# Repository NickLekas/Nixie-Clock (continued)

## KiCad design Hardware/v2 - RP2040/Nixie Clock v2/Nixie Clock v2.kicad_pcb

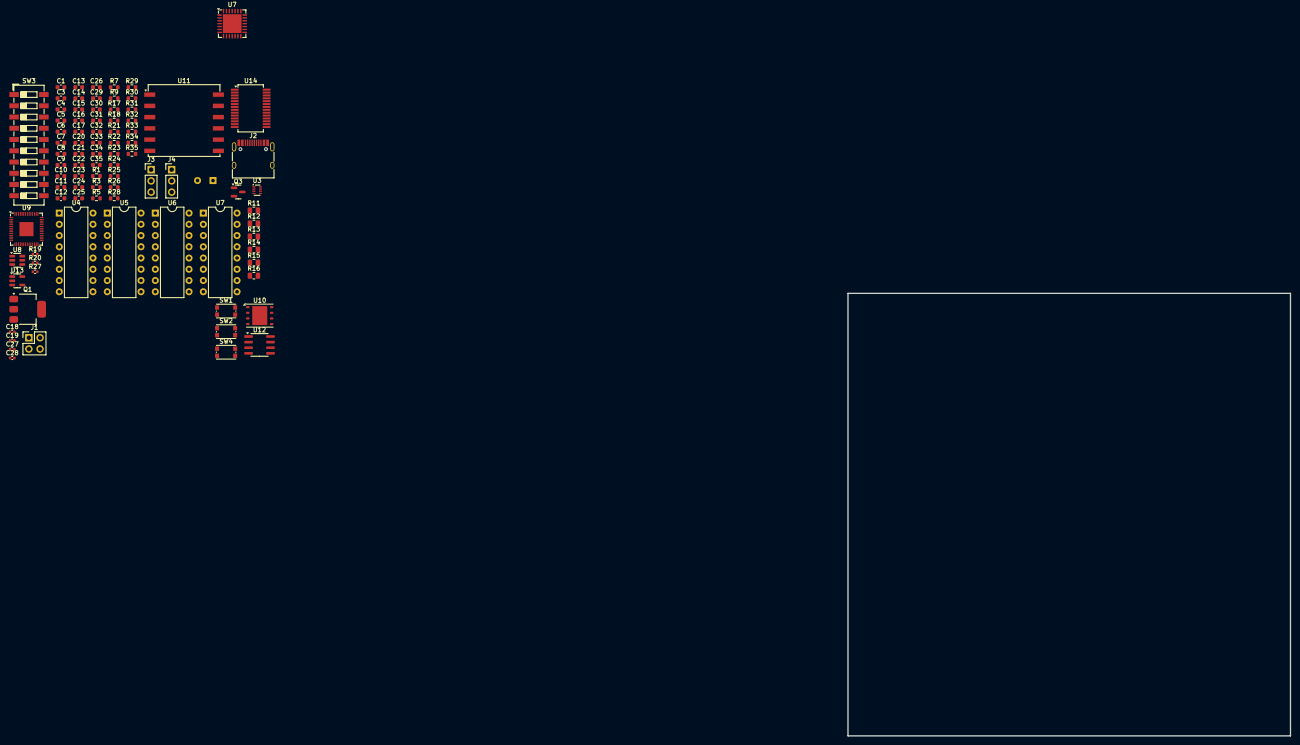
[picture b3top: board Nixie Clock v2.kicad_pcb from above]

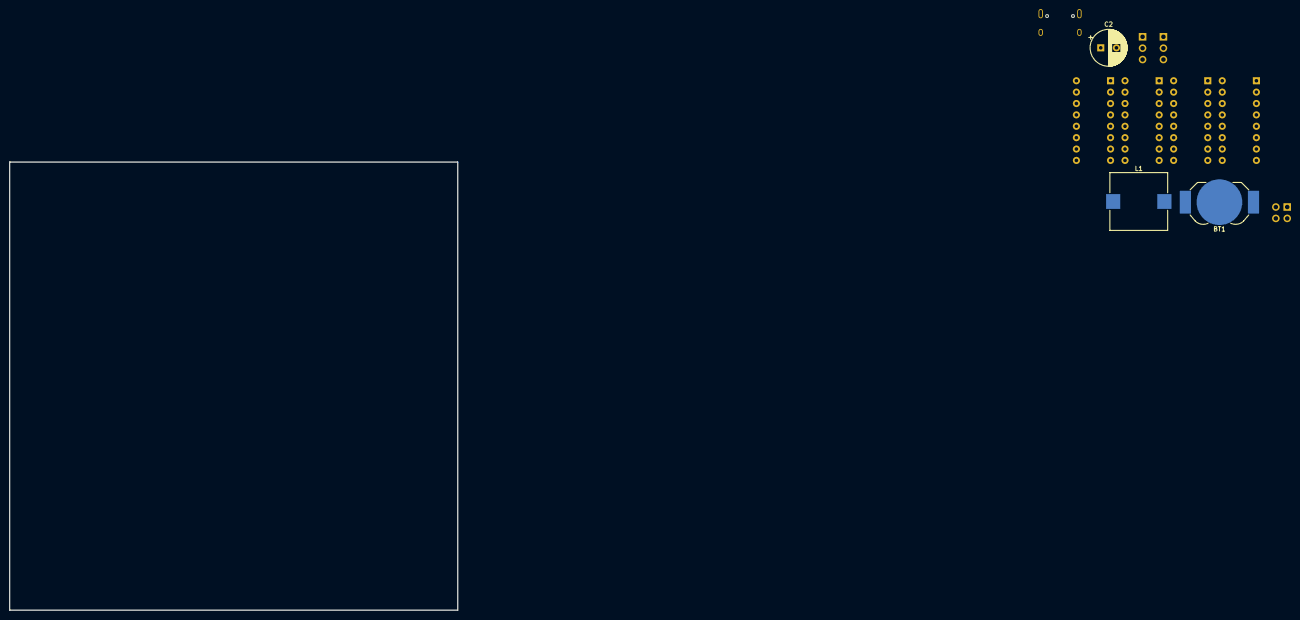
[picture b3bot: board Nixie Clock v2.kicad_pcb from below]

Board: 2 copper layers, 100.0 x 100.0 mm, 90 parts (3 on the bottom side), 82 nets, no tracks yet.

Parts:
BT1: CR1220; BatteryHolder_LINX_BAT-HLD-012-SMT
C1: 100u; C_0603_1608Metric
C2: 4.7u; CP_Radial_D8.0mm_P3.50mm
C3, C5, C9, C10, C11, C12, C13, C14, C15, C16, C17, C20, C21, C24, C25, C29, C33, C35: 100n; C_0603_1608Metric
C4, C26: 10u; C_0603_1608Metric
C6: 82p; C_0603_1608Metric
C7: 33n; C_0603_1608Metric
C8: 47u; C_0603_1608Metric
C18, C19: 1u; C_0402_1005Metric
C22, C23, C30, C31, C34: 1u; C_0603_1608Metric
C27, C28: 8p; C_0402_1005Metric
C32: 10n; C_0603_1608Metric
J1: Conn_02x02_2.54mm; PinHeader_2x02_P2.54mm_Vertical
J2: USB_C_Receptacle_USB2.0; USB_C_Receptacle_HRO_TYPE-C-31-M-12
J3, J4: Conn_01x03_2.54mm; PinHeader_1x03_P2.54mm_Vertical
L1: 7.8u; L_Vishay_IHLP-5050
Q1: PZTA92; SOT-223-3_TabPin2
Q3: MMBTA42; SOT-23
R1, R3, R5: 100k; R_0603_1608Metric
R7, R9, R18, R23, R24, R26, R30, R31, R32, R35: 10k; R_0603_1608Metric
R11, R12, R15, R16: 22k; R_0805_2012Metric
R13, R14: 220k; R_0805_2012Metric
R17: 30.9; R_0603_1608Metric
R19, R20: 27.4; R_0402_1005Metric
R21, R22: 5.1k; R_0603_1608Metric
R25: 1k; R_0603_1608Metric
R27: 1k; R_0402_1005Metric
R28, R29: 2.2k; R_0603_1608Metric
R33: R_Photo; R_0603_1608Metric
R34: 150; R_0603_1608Metric
SW1, SW2, SW4: SW_Push; SW_Push_1P1T_NO_CK_KMR2
SW3: SW_DIP_x10; SW_DIP_SPSTx10_Slide_6.7x26.96mm_W6.73mm_P2.54mm_LowProfile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
U3: TPS62933; SOT-583-8
U4, U5, U6, U7#2: К155ИД1; DIP-16_W7.62mm
U7: MCP23017_ML; QFN-28-1EP_6x6mm_P0.65mm_EP4.25x4.25mm
U8: AP22913; SOT-23-6
U9: RP2040; QFN-56-1EP_7x7mm_P0.4mm_EP3.2x3.2mm
U10: W25Q128JVP; WSON-8-1EP_6x5mm_P1.27mm_EP3.4x4.3mm
U11: L80-M39; Quectel_L80-R
U12: DS3231MZ; SOIC-8_3.9x4.9mm_P1.27mm
U13: TC2185-3.3VCTTR; SOT-23-5
U14: MCP23017_SS; SSOP-28_5.3x10.2mm_P0.65mm

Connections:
+1V1: C9.1, C10.1, C18.1, U9.23 (DVDD), U9.45 (VREG_VOUT), U9.50 (DVDD)
+3.3V: C6.1, C8.1, C11.1, C12.1, C13.1, C14.1, C15.1, C16.1, C17.1, C19.1, L1.2, R17.2, R23.2, R24.2, U9.1 (IOVDD), U9.10 (IOVDD), U9.22 (IOVDD), U9.33 (IOVDD), U9.42 (IOVDD), U9.43 (ADC_AVDD), U9.44 (VREG_IN), U9.48 (USB_VDD), U9.49 (IOVDD)
+3.3VA: C30.1, R33.1, U13.5 (VOUT)
+3V3: C22.1, C29.1, C33.1, R28.1, R29.1, R30.1, R31.1, R32.1, U7.5 (VDD), U8.4 (VIN), U8.6 (VIN), U10.8 (VCC), U12.2 (VCC), U12.4 (~RST), U14.9 (VDD)
/170V_1: C2.1, Q1.3 (E), R1.1
/ANODE_1: Q1.2 (C), R11.1, R12.1, R13.1, R14.1, R15.1, R16.1
/Dimming: R7.1, R9.1, U9.34 (GPIO22)
/GPS_EN: U8.3 (EN), U9.35 (GPIO23)
/Hours_Ones_A: U5.3 (A), U9.13 (GPIO10)
/Hours_Ones_B: U5.6 (B), U9.14 (GPIO11)
/Hours_Ones_C: U5.7 (C), U9.15 (GPIO12)
/Hours_Ones_D: U5.4 (D), U9.16 (GPIO13)
/Hours_Tens_A: U4.3 (A), U9.4 (GPIO2)
/Hours_Tens_B: U4.6 (B), U9.5 (GPIO3)
/Hours_Tens_C: U4.7 (C), U9.8 (GPIO6)
/Hours_Tens_D: U4.4 (D), U9.9 (GPIO7)
/I2C0 SCL: R29.2, U7.8 (SCK), U9.7 (GPIO5), U12.8 (SCL), U14.12 (SCK)
/I2C0_SDA: R28.2, U7.9 (SDA), U9.6 (GPIO4), U12.7 (SDA), U14.13 (SDA)
/Light: C34.1, R34.2, U9.38 (GPIO26_ADC0)
/Mins_Ones_A: U7#2.3 (A), U9.29 (GPIO18)
/Mins_Ones_B: U7#2.6 (B), U9.30 (GPIO19)
/Mins_Ones_C: U7#2.7 (C), U9.31 (GPIO20)
/Mins_Ones_D: U7#2.4 (D), U9.32 (GPIO21)
/Mins_Tens_A: U6.3 (A), U9.17 (GPIO14)
/Mins_Tens_B: U6.6 (B), U9.18 (GPIO15)
/Mins_Tens_C: U6.7 (C), U9.27 (GPIO16)
/Mins_Tens_D: U6.4 (D), U9.28 (GPIO17)
/RTC_Interrupt: U9.36 (GPIO24), U12.3 (~INT/SQW)
/Settings_Interrupt: R30.2, U7.16 (INTA), U9.37 (GPIO25), U14.20 (INTA)
/UART0 RX: J3.2, U9.3 (GPIO1)
/UART0 TX: J3.3, U9.2 (GPIO0)
/UART1_RX: U9.12 (GPIO9), U11.2 (TXD1)
/UART1_TX: U9.11 (GPIO8), U11.1 (RXD1)
GND: BT1.2 (-), C1.2, C2.2, C4.2, C5.2, C7.2, C8.2, C9.2, C10.2, C11.2, C12.2, C13.2, C14.2, C15.2, C16.2, C17.2, C18.2, C19.2, C20.2, C21.2, C22.2, C23.2, C24.2, C25.2, C26.2, C27.1, C28.1, C29.2, C30.2, C31.2, C32.2, C33.2, C34.2, C35.2, J1.1, J1.3, J2.A1 (GND), J2.A12 (GND), J2.B1 (GND), J2.B12 (GND), J2.S1 (SHIELD), J3.1, J4.2, Q3.2 (E), R9.2, R18.1, R21.1, R22.1, R35.2, SW1.1, SW2.1, SW3.11, SW3.12, SW3.13, SW3.14, SW3.15, SW3.16, SW3.17, SW3.18, SW3.19, SW3.20, SW4.2, U3.4 (GND), U4.12 (GND), U5.12 (GND), U6.12 (GND), U7.6 (VSS), U7.11 (A0), U7.12 (A1), U7.13 (A2), U7.29 (EP), U7#2.12 (GND), U8.2 (GND), U8.5 (GND), U9.19 (TESTEN), U9.57 (GND), U10.4 (GND), U10.9 (EP), U11.3 (GND), U11.7 (TIMER), U11.12 (GND), U12.5 (GND), U13.2 (GND), U14.10 (VSS), U14.15 (A0), U14.16 (A1), U14.17 (A2)
unnamed: BT1.1 (+), U12.6 (VBAT)
unnamed: C21.1, R24.1, R25.2, SW2.2
unnamed: C28.2, R27.2
unnamed: J1.2, R13.2
unnamed: J1.4, R14.2
unnamed: J2.A5 (CC1), R22.2
unnamed: J2.B5 (CC2), R21.2
unnamed: J2.A6 (D+), J2.B6 (D+), R20.2
unnamed: J2.A7 (D-), J2.B7 (D-), R19.2
unnamed: J4.1, U9.24 (SWCLK)
unnamed: J4.3, U9.25 (SWD)
unnamed: Q1.1 (B), R1.2, R3.1
unnamed: Q3.1 (B), R7.2
unnamed: Q3.3 (C), R5.2
unnamed: R3.2, R5.1
unnamed: R33.2, R34.1, R35.1
unnamed: C3.1, U3.6 (BST)
unnamed: C6.2, R17.1, R18.2, U3.8 (FB)
unnamed: C7.1, U3.7 (SS)
unnamed: C3.2, L1.1, U3.5 (SW)
unnamed: SW3.9, U7.17 (GPA0)
unnamed: SW3.10, U7.18 (GPA1)
unnamed: C35.1, SW4.1, U7.19 (GPA2)
unnamed: SW3.1, U7.25 (GPB0)
unnamed: SW3.2, U7.26 (GPB1)
unnamed: SW3.3, U7.27 (GPB2)
unnamed: SW3.4, U7.28 (GPB3)
unnamed: SW3.5, U7.1 (GPB4)
unnamed: SW3.6, U7.2 (GPB5)
unnamed: SW3.7, U7.3 (GPB6)
unnamed: SW3.8, U7.4 (GPB7)
unnamed: R31.2, U7.15 (INTB)
unnamed: R32.2, U7.14 (~RESET)
unnamed: C20.1, R23.1, SW1.2, U9.26 (RUN)
unnamed: R19.1, U9.46 (USB_DM)
unnamed: R20.1, U9.47 (USB_DP)
unnamed: C27.2, U9.20 (XIN)
unnamed: R27.1, U9.21 (XOUT)
unnamed: U9.52 (QSPI_SCLK), U10.6 (CLK)
unnamed: U9.53 (QSPI_SD0), U10.5 (DI(IO0))
unnamed: U9.55 (QSPI_SD1), U10.2 (DO(IO1))
unnamed: U9.54 (QSPI_SD2), U10.3 (IO2)
unnamed: U9.51 (QSPI_SD3), U10.7 (IO3)
unnamed: R25.1, U9.56 (QSPI_SS), U10.1 (~CS)
unnamed: C23.1, C24.1, C25.1, C26.1, R26.1, U8.1 (OUT), U11.4 (VCC), U11.5 (V_BCKP)
unnamed: R26.2, U11.10 (~RESET)
unnamed: C32.1, U13.4 (BP)
VBUS: C1.1, C4.1, C5.1, C31.1, J2.A4 (VBUS), J2.A9 (VBUS), J2.B4 (VBUS), J2.B9 (VBUS), U3.3 (VIN), U4.5 (Vcc), U5.5 (Vcc), U6.5 (Vcc), U7#2.5 (Vcc), U13.1 (VIN), U13.3 (ON/~OFF)

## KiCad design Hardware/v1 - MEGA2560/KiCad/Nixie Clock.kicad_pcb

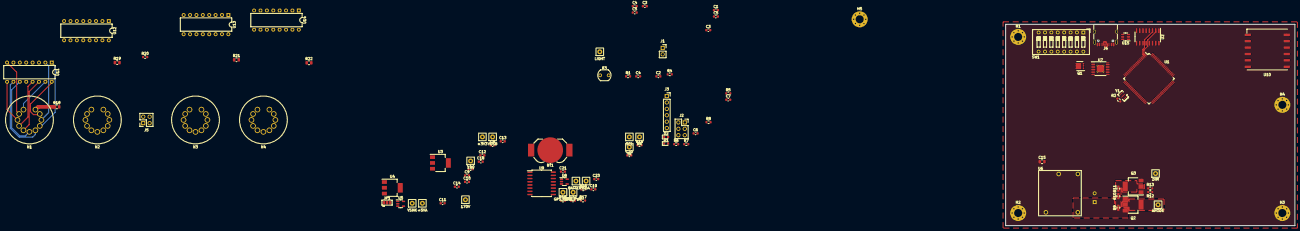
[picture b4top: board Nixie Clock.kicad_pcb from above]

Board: 2 copper layers, 115.0 x 80.0 mm, 102 parts (1 on the bottom side), 117 nets.

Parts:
BT1: Battery_Cell; BatteryHolder_LINX_BAT-HLD-012-SMT
C1, C3, C3#2, C4, C4#2, C5, C5#2, C6, C7, C9, C11, C21, C22: 0u1; C_0603_1608Metric
C2, C18, C23: 10u; C_0603_1608Metric
C8, C10, C14: 2u2; C_0603_1608Metric
C12, C17, C19: 1u; C_0603_1608Metric
C13, C20: 470p; C_0603_1608Metric
C15: 100u; C_0805_2012Metric
C16: 4u7; CP_Radial_D8.0mm_P3.50mm
D1, D2: Green; LED_0603_1608Metric
H1, H2, H3, H4, H5: MountingHole_Pad; MountingHole_3.2mm_M3_Pad_Via
J1: Reset; PinSocket_1x02_P2.54mm_Vertical
J2: ICSP; PinSocket_2x03_P2.54mm_Vertical
J3: Serial; PinSocket_1x06_P2.54mm_Vertical
J4: USB_C_USB2.0; USB_C_Receptacle_HRO_TYPE-C-31-M-12
J5: Colon; PinSocket_2x02_P2.54mm_Vertical
JP1: Voltage Select; SolderJumper-3_P1.3mm_Open_Pad1.0x1.5mm
N1, N2, N3, N4: ИН-8
Q1: CSD18543Q3A; VSON-8_3.3x3.3mm_P0.65mm_NexFET
Q2: PZTA92; SOT-223-3_TabPin2
Q3: PZTA42; SOT-223-3_TabPin2
R1, R4, R12, R13, R14, R15, R17: 10K; R_0603_1608Metric
R2: 1M; R_0603_1608Metric
R3: GM5539; R_LDR_5.1x4.3mm_P3.4mm_Vertical
R5, R6, R7, R8: 5K1; R_0603_1608Metric
R9, R10, R11, R20: 100K; R_0603_1608Metric
R16: 5k1; R_0603_1608Metric
R18, R19, R21, R22: 10K; R_0805_2012Metric
SW1: Settings; SW_DIP_SPSTx08_Slide_9.78x22.5mm_W7.62mm_P2.54mm
TP1: LIGHT; TestPoint_THTPad_D2.0mm_Drill0.9mm
TP2: +5V; TestPoint_THTPad_D2.0mm_Drill0.9mm
TP3: +5VA; TestPoint_THTPad_D2.0mm_Drill0.9mm
TP4: +3V3; TestPoint_THTPad_D2.0mm_Drill0.9mm
TP5: ANODE; TestPoint_THTPad_D2.0mm_Drill0.9mm
TP6: 170V; TestPoint_THTPad_D2.0mm_Drill0.9mm
TP7: VUSB; TestPoint_THTPad_D2.0mm_Drill0.9mm
TP8: VSNK; TestPoint_THTPad_D2.0mm_Drill0.9mm
TP9: DIM; TestPoint_THTPad_D2.0mm_Drill0.9mm
TP10: GPS_PWR; TestPoint_THTPad_D2.0mm_Drill0.9mm
TP11: GPS_CTRL; TestPoint_THTPad_D2.0mm_Drill0.9mm
TP12: RX; TestPoint_THTPad_D2.0mm_Drill0.9mm
TP13: TX; TestPoint_THTPad_D2.0mm_Drill0.9mm
TP14: BATTERY; TestPoint_THTPad_D2.0mm_Drill0.9mm
TP15: SCL; TestPoint_THTPad_D2.0mm_Drill0.9mm
TP16: SDA; TestPoint_THTPad_D2.0mm_Drill0.9mm
U1: ATmega2560-16A; TQFP-100_14x14mm_P0.5mm
U2: CH340C; SOIC-16_3.9x9.9mm_P1.27mm
U3, U4: LM340MP-5.0_SOT223; SOT-223-3_TabPin2
U5, U8: MIC5205-3.3YM5; SOT-23-5
U6: NCH8200HV
U7: IP2721; TSSOP-16-1EP_4.4x5mm_P0.65mm_EP3x3mm_ThermalVias
U9: DS3231SN#T&R; SOIC-16W_7.5x10.3mm_P1.27mm
U10: L80-R; Quectel_L80-R
U11, U12, U13, U14: К155ИД1; DIP-16_W7.62mm
U15: USBLC6-2SC6; SOT-23-6
Y1: 16MHz; Resonator_SMD_Murata_CSTxExxV-3Pin_3.0x1.1mm

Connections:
+3V3: C14.1, R14.1, R15.1, TP4.1, U5.5 (OUT), U9.2 (VCC)
+5V: C3.1, C4.1, C5.1, C9.1, J2.2, J3.4, R1.1, R5.1, R6.1, TP2.1, U1.10 (VCC), U1.31 (VCC), U1.61 (VCC), U1.80 (VCC), U2.16 (VCC), U3.3 (VO), U11.5 (VCC), U12.5 (VCC), U13.5 (VCC), U14.5 (VCC)
+5VA: C11.1, R3.1, TP3.1, U1.98 (AREF), U1.100 (AVCC), U4.3 (VO)
/Communication/USB_IN_D+: J4.A6 (D+), J4.B6 (D+), U15.4 (I/O2)
/Communication/USB_IN_D-: J4.A7 (D-), J4.B7 (D-), U15.6 (I/O1)
/DST: SW1.16, U1.71 (PA7)
/EIGHT: SW1.13, U1.74 (PA4)
/EXTRA1: SW1.9, U1.78 (PA0)
/FOUR: SW1.12, U1.75 (PA3)
/LIGHT: C2.2, R3.2, R4.2, TP1.1, U1.97 (PF0)
/ONE: SW1.10, U1.77 (PA1)
/PLUS_MINUS: SW1.14, U1.73 (PA5)
/TIME_MODE: SW1.15, U1.72 (PA6)
/TWO: SW1.11, U1.76 (PA2)
ANODE: Q2.2 (C), R18.2, R19.2, R20.1, R21.2, R22.2, TP5.1
CC1: J4.A5 (CC1), R7.1, U7.13 (CC1)
CC2: J4.B5 (CC2), R8.1, U7.12 (CC2)
DIM: R12.1, R13.1, TP9.1, U1.5 (PE3)
DTR: C1.1, J3.1, U2.13 (~DTR)
GND: BT1.2 (-), C2.1, C3.2, C3#2.2, C4.2, C4#2.2, C5.2, C5#2.2, C6.2, C7.2, C8.2, C9.2, C10.2, C11.2, C12.2, C13.2, C14.2, C15.2, C16.2, C17.2, C18.2, C19.2, C20.2, C21.2, C22.2, C23.2, H1.1, H2.1, H3.1, H4.1, H5.1, J1.2, J2.6, J3.5, J3.6, J4.A1 (GND), J4.A12 (GND), J4.B1 (GND), J4.B12 (GND), J4.S1 (SHIELD), J5.3, JP1.3 (B), Q3.3 (E), R4.1, R7.2, R8.2, R13.2, R17.1, SW1.1, SW1.2, SW1.3, SW1.4, SW1.5, SW1.6, SW1.7, SW1.8, U1.11 (GND), U1.32 (GND), U1.62 (GND), U1.81 (GND), U1.99 (GND), U2.1 (GND), U3.2 (GND), U4.2 (GND), U5.2 (GND), U6.3 (GND), U6.4 (GND), U7.5 (GND), U8.2 (GND), U9.5 (GND), U9.6 (GND), U9.7 (GND), U9.8 (GND), U9.9 (GND), U9.10 (GND), U9.11 (GND), U9.12 (GND), U9.13 (GND), U10.3 (GND), U10.12 (GND), U11.12 (GND), U12.12 (GND), U13.12 (GND), U14.12 (GND), U15.2 (GND), Y1.2
GPS_CTRL: TP11.1, U1.70 (PG2), U8.3 (EN)
GPS_RX: R16.2, U1.63 (PJ0)
GPS_TX: TP12.1, U1.64 (PJ1), U10.2 (TXD1)
HOA: U1.42 (PL7), U12.3 (A)
HOB: U1.40 (PL5), U12.6 (B)
HOC: U1.39 (PL4), U12.7 (C)
HOD: U1.41 (PL6), U12.4 (D)
HTA: U1.38 (PL3), U11.3 (A)
HTB: U1.36 (PL1), U11.6 (B)
HTC: U1.35 (PL0), U11.7 (C)
HTD: U1.37 (PL2), U11.4 (D)
MISO: J2.1, U1.22 (PB3)
MOA: U1.60 (PC7), U14.3 (A)
MOB: U1.58 (PC5), U14.6 (B)
MOC: U1.57 (PC4), U14.7 (C)
MOD: U1.59 (PC6), U14.4 (D)
MOSI: J2.4, U1.21 (PB2)
MTA: U1.56 (PC3), U13.3 (A)
MTB: U1.54 (PC1), U13.6 (B)
MTC: U1.53 (PC0), U13.7 (C)
MTD: U1.55 (PC2), U13.4 (D)
unnamed: BT1.1 (+), TP14.1, U9.14 (VBAT)
unnamed: C3#2.1, C4#2.1, C5#2.1
unnamed: C6.1, U2.4 (V3)
unnamed: C7.1, U2.15 (R232)
unnamed: C13.1, U5.4 (BP)
unnamed: C16.1, Q2.3 (E), R9.1, TP6.1, U6.2 (VOUT)
unnamed: C20.1, U8.4 (BP)
unnamed: C21.1, C22.1, C23.1, TP10.1, U8.5 (OUT), U10.4 (VCC), U10.5 (V_BCKP)
unnamed: D1.2 (A), R5.2
unnamed: D2.2 (A), R6.2
unnamed: J5.1, R20.2
unnamed: J5.2, J5.4
unnamed: JP1.2 (C), U7.11 (SEL)
unnamed: N1.1 (Anode), R18.1
unnamed: N1.2 (0), U11.16 (0)
unnamed: N1.3 (9), U11.2 (9)
unnamed: N1.4 (8), U11.1 (8)
unnamed: N1.5 (7), U11.10 (7)
unnamed: N1.6, U11.11 (6)
unnamed: N1.7 (5), U11.14 (5)
unnamed: N1.8 (4), U11.13 (4)
unnamed: N1.9 (3), U11.9 (3)
unnamed: N1.10 (2), U11.8 (2)
unnamed: N1.11 (1), U11.15 (1)
unnamed: N2.1 (Anode), R19.1
unnamed: N2.2 (0), U12.16 (0)
unnamed: N2.3 (9), U12.2 (9)
unnamed: N2.4 (8), U12.1 (8)
unnamed: N2.5 (7), U12.10 (7)
unnamed: N2.6, U12.11 (6)
unnamed: N2.7 (5), U12.14 (5)
unnamed: N2.8 (4), U12.13 (4)
unnamed: N2.9 (3), U12.9 (3)
unnamed: N2.10 (2), U12.8 (2)
unnamed: N2.11 (1), U12.15 (1)
unnamed: N3.1 (Anode), R21.1
unnamed: N3.2 (0), U13.16 (0)
unnamed: N3.3 (9), U13.2 (9)
unnamed: N3.4 (8), U13.1 (8)
unnamed: N3.5 (7), U13.10 (7)
unnamed: N3.6, U13.11 (6)
unnamed: N3.7 (5), U13.14 (5)
unnamed: N3.8 (4), U13.13 (4)
unnamed: N3.9 (3), U13.9 (3)
unnamed: N3.10 (2), U13.8 (2)
unnamed: N3.11 (1), U13.15 (1)
unnamed: N4.1 (Anode), R22.1
unnamed: N4.2 (0), U14.16 (0)
unnamed: N4.3 (9), U14.2 (9)
unnamed: N4.4 (8), U14.1 (8)
unnamed: N4.5 (7), U14.10 (7)
unnamed: N4.6, U14.11 (6)
unnamed: N4.7 (5), U14.14 (5)
unnamed: N4.8 (4), U14.13 (4)
unnamed: N4.9 (3), U14.9 (3)
unnamed: N4.10 (2), U14.8 (2)
unnamed: N4.11 (1), U14.15 (1)
unnamed: Q1.4 (G), U7.1 (VBUSG)
unnamed: Q2.1 (B), R9.2, R10.1
unnamed: Q3.1 (B), R12.2
unnamed: Q3.2 (C), R11.2
unnamed: R2.1, U1.34 (XTAL1), Y1.1
unnamed: R2.2, U1.33 (XTAL2), Y1.3
unnamed: R10.2, R11.1
unnamed: R16.1, R17.2, TP13.1, U10.1 (RXD1)
RST: C1.2, J1.1, J2.5, R1.2, U1.30 (~RESET)
RTC_INT: U1.6 (PE4), U9.3 (~INT~/SQW)
RXI: D1.1 (K), J3.2, U1.3 (PE1), U2.3 (RXD)
SCK: J2.3, U1.20 (PB1)
SCL: R15.2, TP15.1, U9.16 (SCL)
SDA: R14.2, TP16.1, U9.15 (SDA)
TXO: D2.1 (K), J3.3, U1.2 (PE0), U2.2 (TXD)
USB_D+: U2.5 (UD+), U15.3 (I/O2)
USB_D-: U2.6 (UD-), U15.1 (I/O1)
VSNK: C8.1, C10.1, C12.1, C15.1, C18.1, C19.1, Q1.5 (D), TP8.1, U3.1 (VI), U4.1 (VI), U5.1 (IN), U5.3 (EN), U6.1 (VCC), U7.16 (VBUS), U8.1 (IN)
VUSB: C17.1, J4.A4 (VBUS), J4.A9 (VBUS), J4.B4 (VBUS), J4.B9 (VBUS), JP1.1 (A), Q1.1 (S), Q1.2 (S), Q1.3 (S), TP7.1, U7.2 (VIN), U15.5 (VBUS)

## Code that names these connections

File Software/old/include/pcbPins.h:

#ifndef PCBPINS_H
#define PCBPINS_H

//GPS pins
#define gpsSerial Serial3 //RX:PJ0 TX:PJ1
const int gpsCtrl = 39; //PG2

//dimming pins
const int dim = 5; //PG5
const int light = 54; //A0 PF0

//dip switch pins
//time set pins
const int dst = 29; //1 PA7
const int timeMode = 28; //2 PA6
const int plusMinus = 27; //3 PA5
const int eight = 26; //4 PA4
const int four = 25; //5 PA3
const int two = 24; //6 PA2
const int one = 23; //7 PA1
//extra pin allotted for latter potential expansion
const int extra1 = 22; //8 PA0

//digit pins
//minutes ones
const int minOnesA = 30; //PC7
const int minOnesB = 32; //PC5
const int minOnesC = 33; //PC4
const int minOnesD = 31; //PC6

//minutes tens
const int minTensA = 34; //PC3
const int minTensB = 36; //PC1
const int minTensC = 37; //PC0
const int minTensD = 35; //PC2

//hours ones
const int hrOnesA = 42; //PL7
const int hrOnesB = 44; //PL5
const int hrOnesC = 45; //PL4
const int hrOnesD = 43; //PL6

//hours tens
const int hrTensA = 46; //PL3
const int hrTensB = 48; //PL1
const int hrTensC = 49; //PL0
const int hrTensD = 47; //PL2

//RTC
const int rtcInt = 2; //PE4

#endif

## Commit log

2019-09-13 Removed build_flags from platfromio.ini
2019-09-13 REmoved build_flages from platformio.ini
2019-09-13 Added basic RTC functionality
2019-09-13 added comments to code
2019-09-13 Added Serial debug messages
2019-09-13 added settings.json to gitignore
2019-09-14 added link to new RTC library
2019-09-14 Added daily RTC time update using GPS
2019-09-14 Changed GPS pins and added GPS power control pin
2019-09-14 Tweakedtime update function
2019-09-14 Changed variable names
2019-09-14 Fixed syntax error
2019-09-14 Disabled nightly time update
2019-09-14 Removed manufaturing files from the PCF8574 library
2019-09-15 Seperated nixie control, gps, and rtc functions into their own files
2019-09-15 Added missing header file to gps.h
2019-09-15 Added GPS power control functions
2019-09-15 Implemented turning the GPS on and off when updating the time
2019-09-18 improved code efficency
2019-09-24 fixed formatting
2019-11-06 Added daylight savings toggle and moved confg file
2019-12-18 changed pin definitions from defines to const ints and added dip switch time zone functionality
2019-12-18 moved the timezone set code from getRTCTime() to setRTCtime to improve efficiency
2019-12-18 changed 12 hour mode secection to a dip switch
2019-12-18 changes the nixie pinmode setup for loop form a hard coded range to the variable numbers
2019-12-18 changed dip switch pins
2019-12-19 added ProMini to platform.ini
2020-01-27 changed to arduino mega, re-assigned pins, adjusted functions to work without IO expanders
2020-01-27 removed all IO expander coder and added propper RTC initiation
2020-02-02 removed all reference to the IO expander and atmega328p controllers
2020-02-02 removed IO expander library call in nixie.h
2020-02-02 added library comments
2020-03-25 removed main.h
2020-03-25 moved header files to the include folder
2020-03-25 changed config to debug
2020-03-25 added light based nixie dimming
2020-03-25 removed delay every 60 seconds for time checking and implemented light based dimming
2020-03-26 added switch labels
2020-03-26 added pcb pins file and a toggle to switch between pins files in debug
2020-03-26 added pcb pins and ic labels
2020-03-26 added rtc interupt pin
2020-03-26 rearranged pcb pins
2020-03-27 moved switch reading from setRTCTime() to dedicated function that runs in getRTCTime()
2020-03-27 moved the time bound check from readSettings() to getRTCTime()
2020-03-28 added a call to dimming durring setup()
2020-03-28 modified dimming() to work with the LDR
2020-03-31 Added PWM minimum bounding and a pull to full brightness when close to max
2020-04-03 Added new PWM functions to lower frequency
2020-04-06 changed dimming pin to work with the PWM frequency library
2020-04-06 rearranged setting switch functions
2020-04-08 Added a dimming function that uses a pot for PWM tuning and lowered the min PWM value for 60Hz
2020-04-15 lowered voltage to trigger max brightness
2020-04-15 added rtc power loss recovery
2020-04-15 set tube brightness to max durrring setup
2020-04-15 removed powerloss check invert to work corectly
2020-04-15 fixed initial pwm write argument order
2020-04-15 removed duplicate call to GPSInit()
2020-04-15 added fade down to brighntess after startup
2020-04-18 refreshed libraries
2020-04-18 added averaging to the light value
2020-12-26 updated libraries
2020-12-26 removed the need for software serial from the GPS library
2020-12-27 Removed averaging code that was causing the PWM signal to be unstable
2020-12-29 Found the ideal PWM frequency and added a 4.7uF capacitor to the output of the nixie supply to eliminate audible coil whine
2020-12-30 Modified to use the new npn dimming circuit
2020-12-30 Improved comments
2020-12-30 Changed the display update to only update the display if the time has changed
2020-12-31 Fixed minor formmating issues
2021-01-04 Adjusted the maxPWM value for the new current limiting resistors
2021-01-04 Added more control over debug options
2021-01-04 Initial commit of the power control code
2021-01-04 Changed programPD() to be hardcoded for 9V 2A (18W) instead of user controllable
2021-01-04 fixed order of operation error and found that wrire() was missing at the end of programPD()
2021-05-21 Change pin assignments to match the PCB
2021-05-26 Create Software
2021-05-26 Delete Software
    Accidentally added
2021-05-26 Create test
2021-05-26 Moved all code to the Softwalre folder
2021-05-26 Started tracking the Software folder
2021-05-26 Added PCB files to Hardware
2021-05-29 Added a toggle to set the RTS using current time when uploading code
2021-05-29 Changed the PWM pin from 4 to 5
2021-05-29 Added 1 second delay when polling the GPS for new data
2021-05-29 Changed the settings pins initilization order to match the PCB pin order
2021-05-29 Seperated minute and hour pin initilazation to match the PCB pin order and disabled PWM frequency control. PWM frequency control will be added back latter
2021-05-29 Added the ability to set RTC time when uploading code and switched from signed binary to multiply by -1 for setting the time zone
2021-05-29 Stoped tracking the eagle project file and added a gitignorefile
2021-05-29 Set PWM to 120Hz using register control
2021-06-01 rearranged the hardware file structure and added the KiCad files
2021-06-01 Moved all KiCad files into a dedicated folder
2021-06-01 added comments about KiCad version used and what v1.05 is
2021-06-02 Added a minimum PWM value to keep the tubes from turning off or partially igniting in the dark
2021-09-22 Create README.md
    initial readme commit
2021-09-22 Create LICENSE
2021-10-10 Update LICENSE
2022-07-21 Redoing code to be more efficent
2022-07-21 worked on initial file setup, completed initial nixie.cpp
2022-07-21 completed settings.h initial code
2023-09-29 Added folders for v2 and started hardware design
2023-10-14 added schematic pages and HV switching circuit
2023-10-22 Complteted schematic, mergerd schematic on to one sheet, started assigning footprints
2023-10-22 removed empty schematic sheets left from the 1 page merge
2023-10-23 Finished assigning footprints and started layout
2023-10-23 Continued work on layout
2024-08-23 replaced old nixie compontes with new library and replaced IO expander with QFN
2024-08-24 Creating seperate processing and nixie boards for furture modularity
2024-08-25 seperated the processor and nixie boards
2024-08-27 Assigned footprints
2024-09-01 Started board layout
2024-09-02 Laied out indivdual circuit blocks
2024-09-02 Started placing assembled blocks on the board and routing
2024-09-02 started nixie layout, added bleed resistor to HV cap
2024-09-02 Completed initial layout of the IN-8 board
2024-09-03 finished initial layout and swapped SDA/SCL on connector
2025-02-03 added ground via stitching, and baord names, version, designer, and date to silkscreen
